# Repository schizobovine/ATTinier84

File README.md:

# ATTinier84
Smallish form factor ATTiny84 platform that doesn't bother with USB.

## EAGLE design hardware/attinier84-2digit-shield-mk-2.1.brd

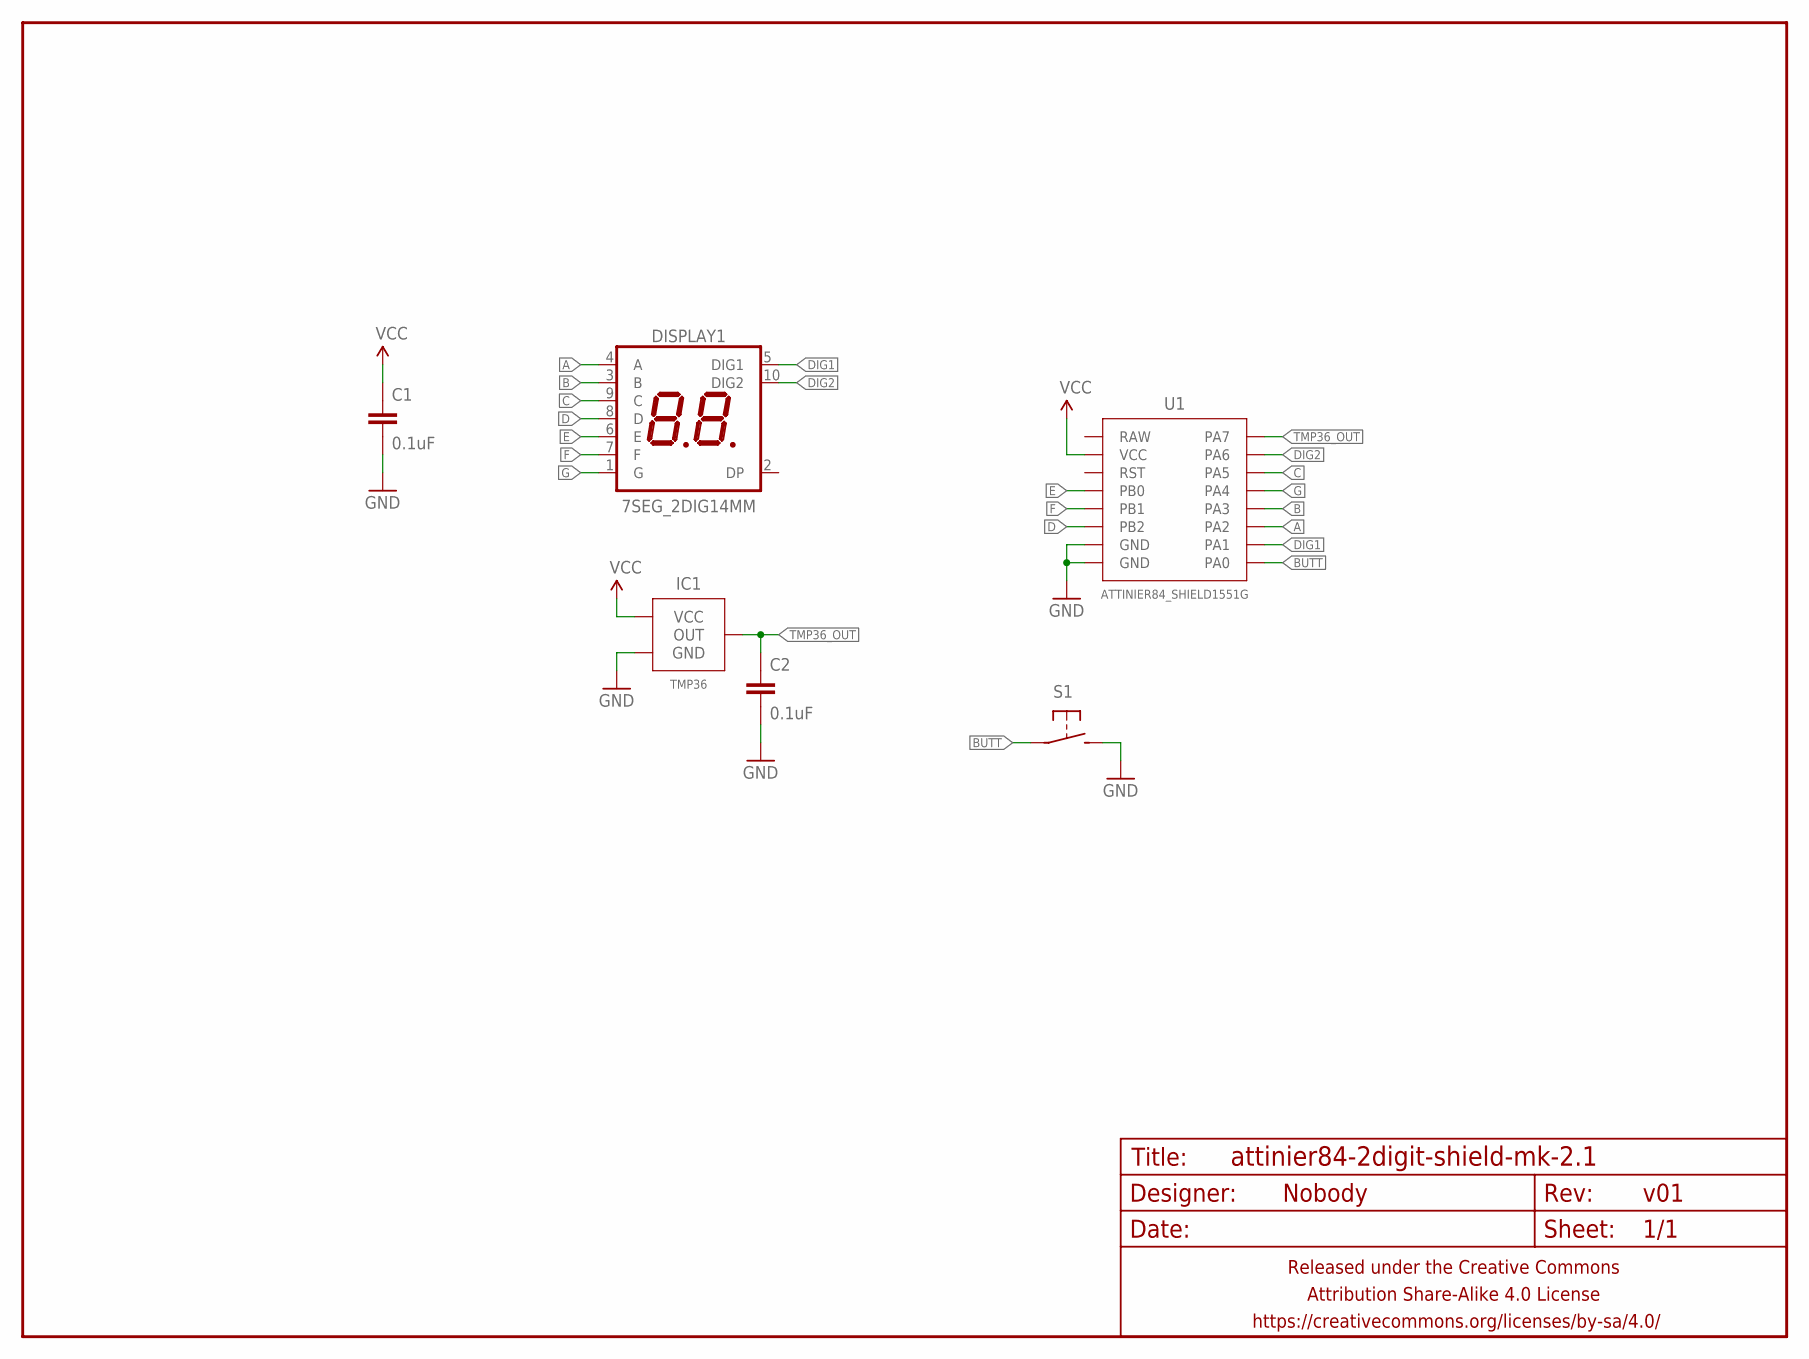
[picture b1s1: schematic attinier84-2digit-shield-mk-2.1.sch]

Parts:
C1, C2: 0.1uF; C025-024X044
DISPLAY1: 7SEG_2DIG14MM; 7SEG_2DIG_14MM
FRAME1: FRAME-LETTERNO_PACKAGE; DUMMY
IC1: TMP36; TO-92-AMMO
S1: SPST-NO-TACT3MM-PTH-SMALL-PADS; DTS-3-SMALL-PADS
U1: ATTINIER84_SHIELD1551G; ATTINIER84_SHIELD2

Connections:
A: DISPLAY1.4 (A), U1.PA2
B: DISPLAY1.3 (B), U1.PA3
BUTT: S1.1, U1.PA0
C: DISPLAY1.9 (C), U1.PA5
D: DISPLAY1.8 (D), U1.PB2
DIG1: DISPLAY1.5 (DIG1), U1.PA1
DIG2: DISPLAY1.10 (DIG2), U1.PA6
E: DISPLAY1.6 (E), U1.PB0
F: DISPLAY1.7 (F), U1.PB1
G: DISPLAY1.1 (G), U1.PA4
GND: C1.2, C2.2, IC1.3 (GND), S1.2, U1.GND@1 (GND), U1.GND@2 (GND)
TMP36_OUT: C2.1, IC1.2 (OUT), U1.PA7
VCC: C1.1, IC1.1 (VCC), U1.VCC

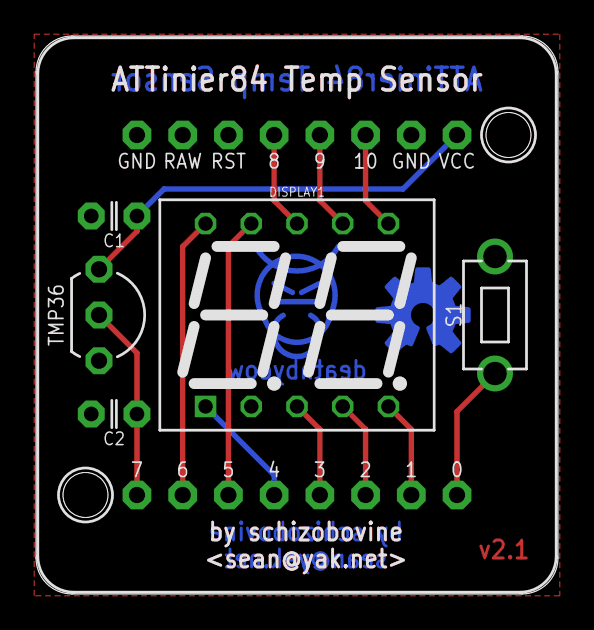
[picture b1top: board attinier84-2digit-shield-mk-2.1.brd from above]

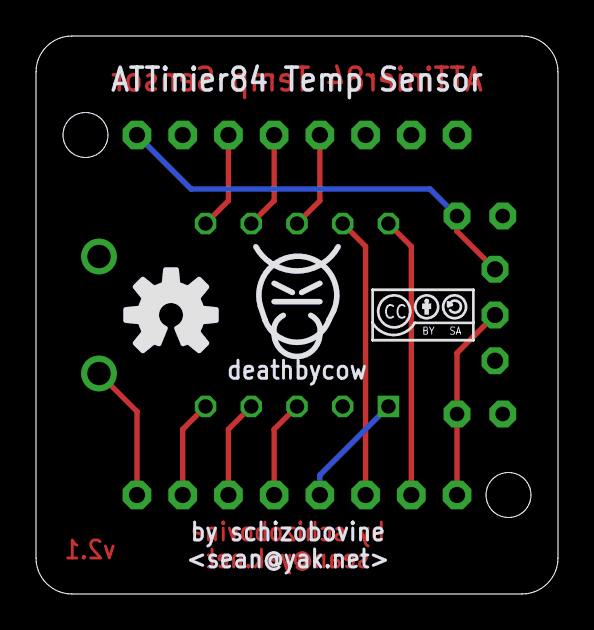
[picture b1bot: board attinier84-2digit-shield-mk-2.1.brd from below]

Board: 2 copper layers, 29.0 x 31.0 mm, 10 parts (2 on the bottom side), 13 nets.

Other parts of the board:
U$1: CC-BY-SA-4.0-NO-URL
U$2: COW_SMALL_METAL
U$3: OSHWLOGO_BOT_0.2_A

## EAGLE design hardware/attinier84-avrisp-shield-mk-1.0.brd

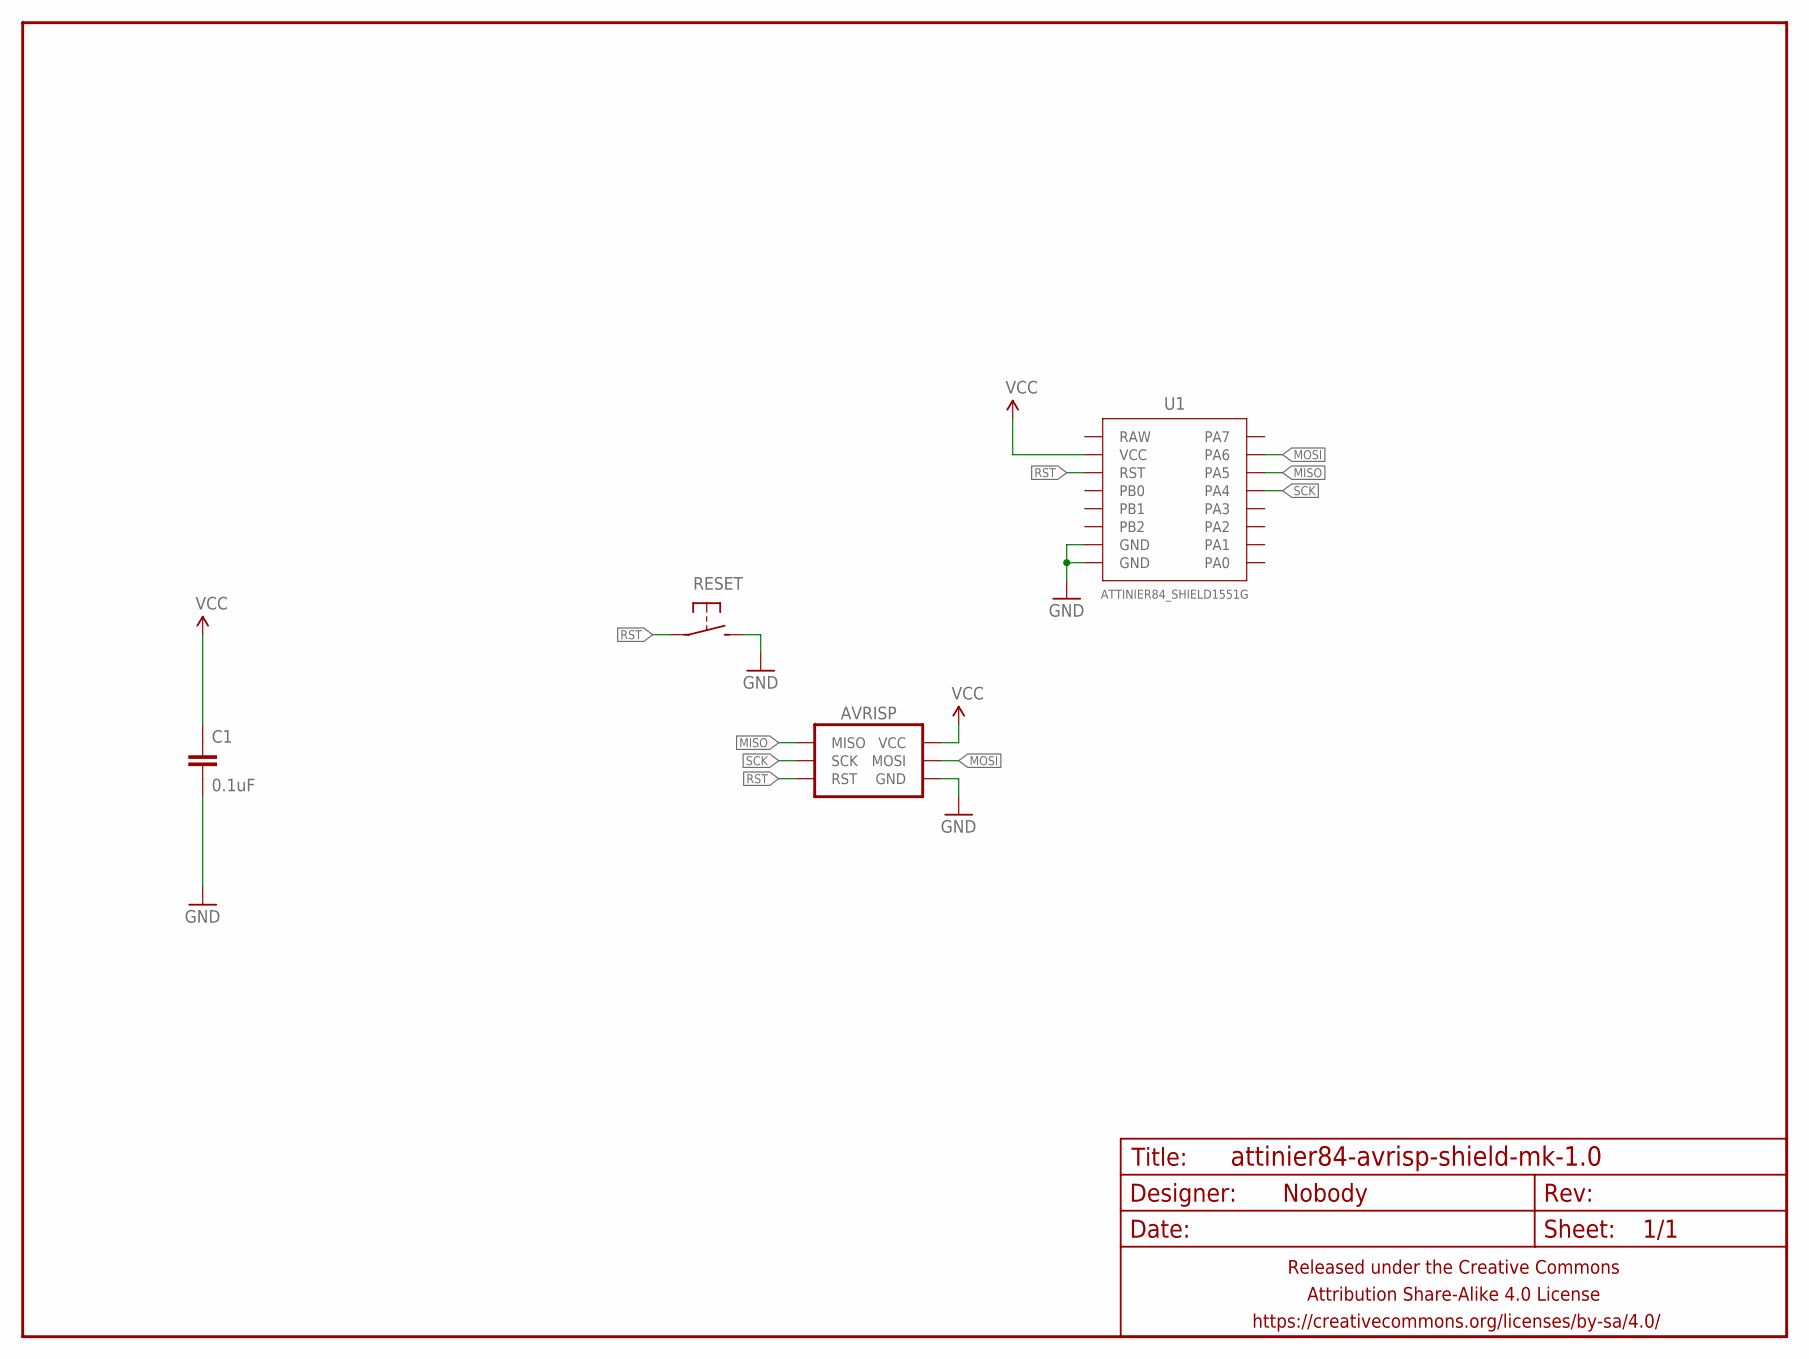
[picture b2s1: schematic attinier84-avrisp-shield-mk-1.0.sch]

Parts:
AVRISP: AVR_SPI_PRG_6PTH-SHROUD; 2X3-SHROUDED
C1: 0.1uF; C025-024X044
FRAME1: FRAME-LETTERNO_PACKAGE; DUMMY
RESET: SPST-NO-TACT6MM-PTH-SMALL-PADS; DTS-6-SMALL-PADS
U1: ATTINIER84_SHIELD1551G; ATTINIER84_SHIELD2

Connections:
GND: AVRISP.6 (GND), C1.2, RESET.3 (2), RESET.4 (2), U1.GND@1 (GND), U1.GND@2 (GND)
MISO: AVRISP.1 (MISO), U1.PA5
MOSI: AVRISP.4 (MOSI), U1.PA6
RST: AVRISP.5 (RST), RESET.1, RESET.2 (1), U1.RST
SCK: AVRISP.3 (SCK), U1.PA4
VCC: AVRISP.2 (VCC), C1.1, U1.VCC

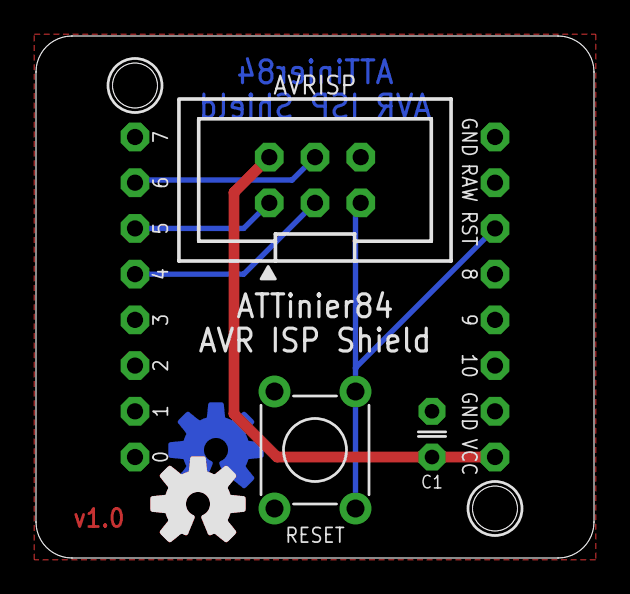
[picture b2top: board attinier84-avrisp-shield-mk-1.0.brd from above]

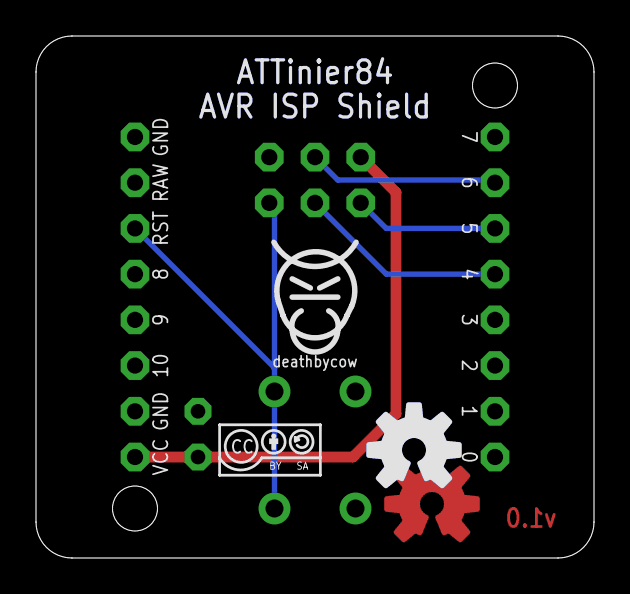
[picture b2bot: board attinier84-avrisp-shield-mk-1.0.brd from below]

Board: 2 copper layers, 31.0 x 29.0 mm, 9 parts (3 on the bottom side), 6 nets.

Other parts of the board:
U$1: CC-BY-SA-4.0-NO-URL
U$2: COW_SMALL
U$3, U$4: OSHWLOGO_BOT_0.2_A

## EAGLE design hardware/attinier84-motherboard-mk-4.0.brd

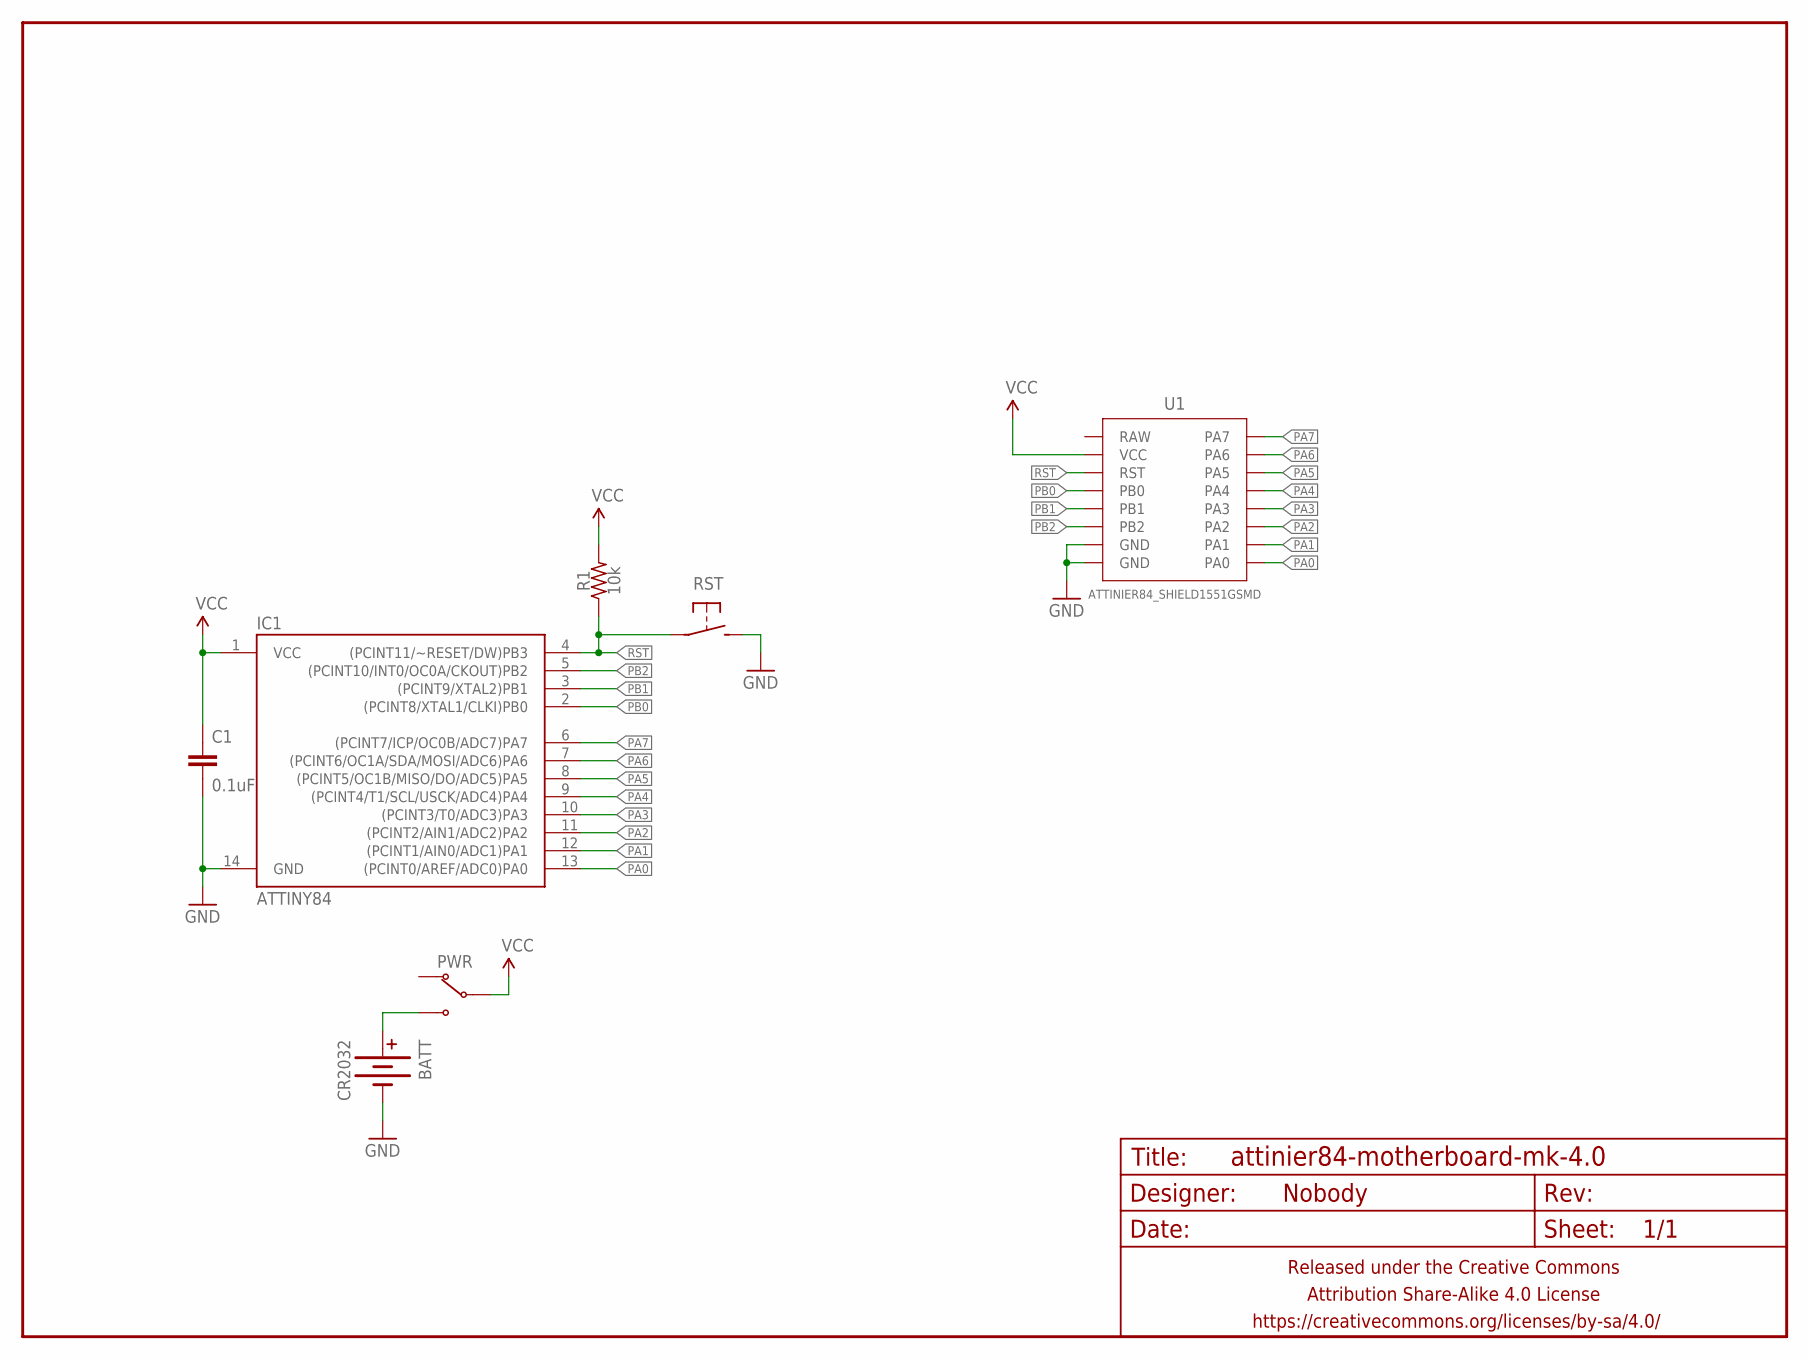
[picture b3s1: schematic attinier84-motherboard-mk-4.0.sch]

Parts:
BATT: CR2032; BATTCON_20MM_MINE_STAHPIT
C1: 0.1uF; C0805
FRAME1: FRAME-LETTERNO_PACKAGE; DUMMY
IC1: ATTINY84; SO14
PWR: SWITCH-SPDTPTH-RA-2.54MM; SPDT-RA-2.54MM
R1: 10k; R0805
RST: SPST-NO-TACTCK-PTS840-GK; TACTILE-SMD-CK-PTS840-GK
U1: ATTINIER84_SHIELD1551GSMD; ATTINIER84_SHIELD2_SMD

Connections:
GND: BATT.BOTTOM (-), C1.2, IC1.14 (GND), RST.3 (2), RST.4 (2), U1.GND@1 (GND), U1.GND@2 (GND)
unnamed: BATT.TOP@1 (+), BATT.TOP@2 (+), PWR.3 (NO)
PA0: IC1.13 ((PCINT0/AREF/ADC0)PA0), U1.PA0
PA1: IC1.12 ((PCINT1/AIN0/ADC1)PA1), U1.PA1
PA2: IC1.11 ((PCINT2/AIN1/ADC2)PA2), U1.PA2
PA3: IC1.10 ((PCINT3/T0/ADC3)PA3), U1.PA3
PA4: IC1.9 ((PCINT4/T1/SCL/USCK/ADC4)PA4), U1.PA4
PA5: IC1.8 ((PCINT5/OC1B/MISO/DO/ADC5)PA5), U1.PA5
PA6: IC1.7 ((PCINT6/OC1A/SDA/MOSI/ADC6)PA6), U1.PA6
PA7: IC1.6 ((PCINT7/ICP/OC0B/ADC7)PA7), U1.PA7
PB0: IC1.2 ((PCINT8/XTAL1/CLKI)PB0), U1.PB0
PB1: IC1.3 ((PCINT9/XTAL2)PB1), U1.PB1
PB2: IC1.5 ((PCINT10/INT0/OC0A/CKOUT)PB2), U1.PB2
RST: IC1.4 ((PCINT11/~RESET/DW)PB3), R1.1, RST.1, RST.2 (1), U1.RST
VCC: C1.1, IC1.1 (VCC), PWR.2 (COM), R1.2, U1.VCC

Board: 2 copper layers, 11 parts (3 on the bottom side), 15 nets, no tracks yet.

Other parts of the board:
U$1: CC-BY-SA-4.0-NO-URL
U$2: COW_SMALL
U$4: OSHWLOGO_BOT_0.2_A

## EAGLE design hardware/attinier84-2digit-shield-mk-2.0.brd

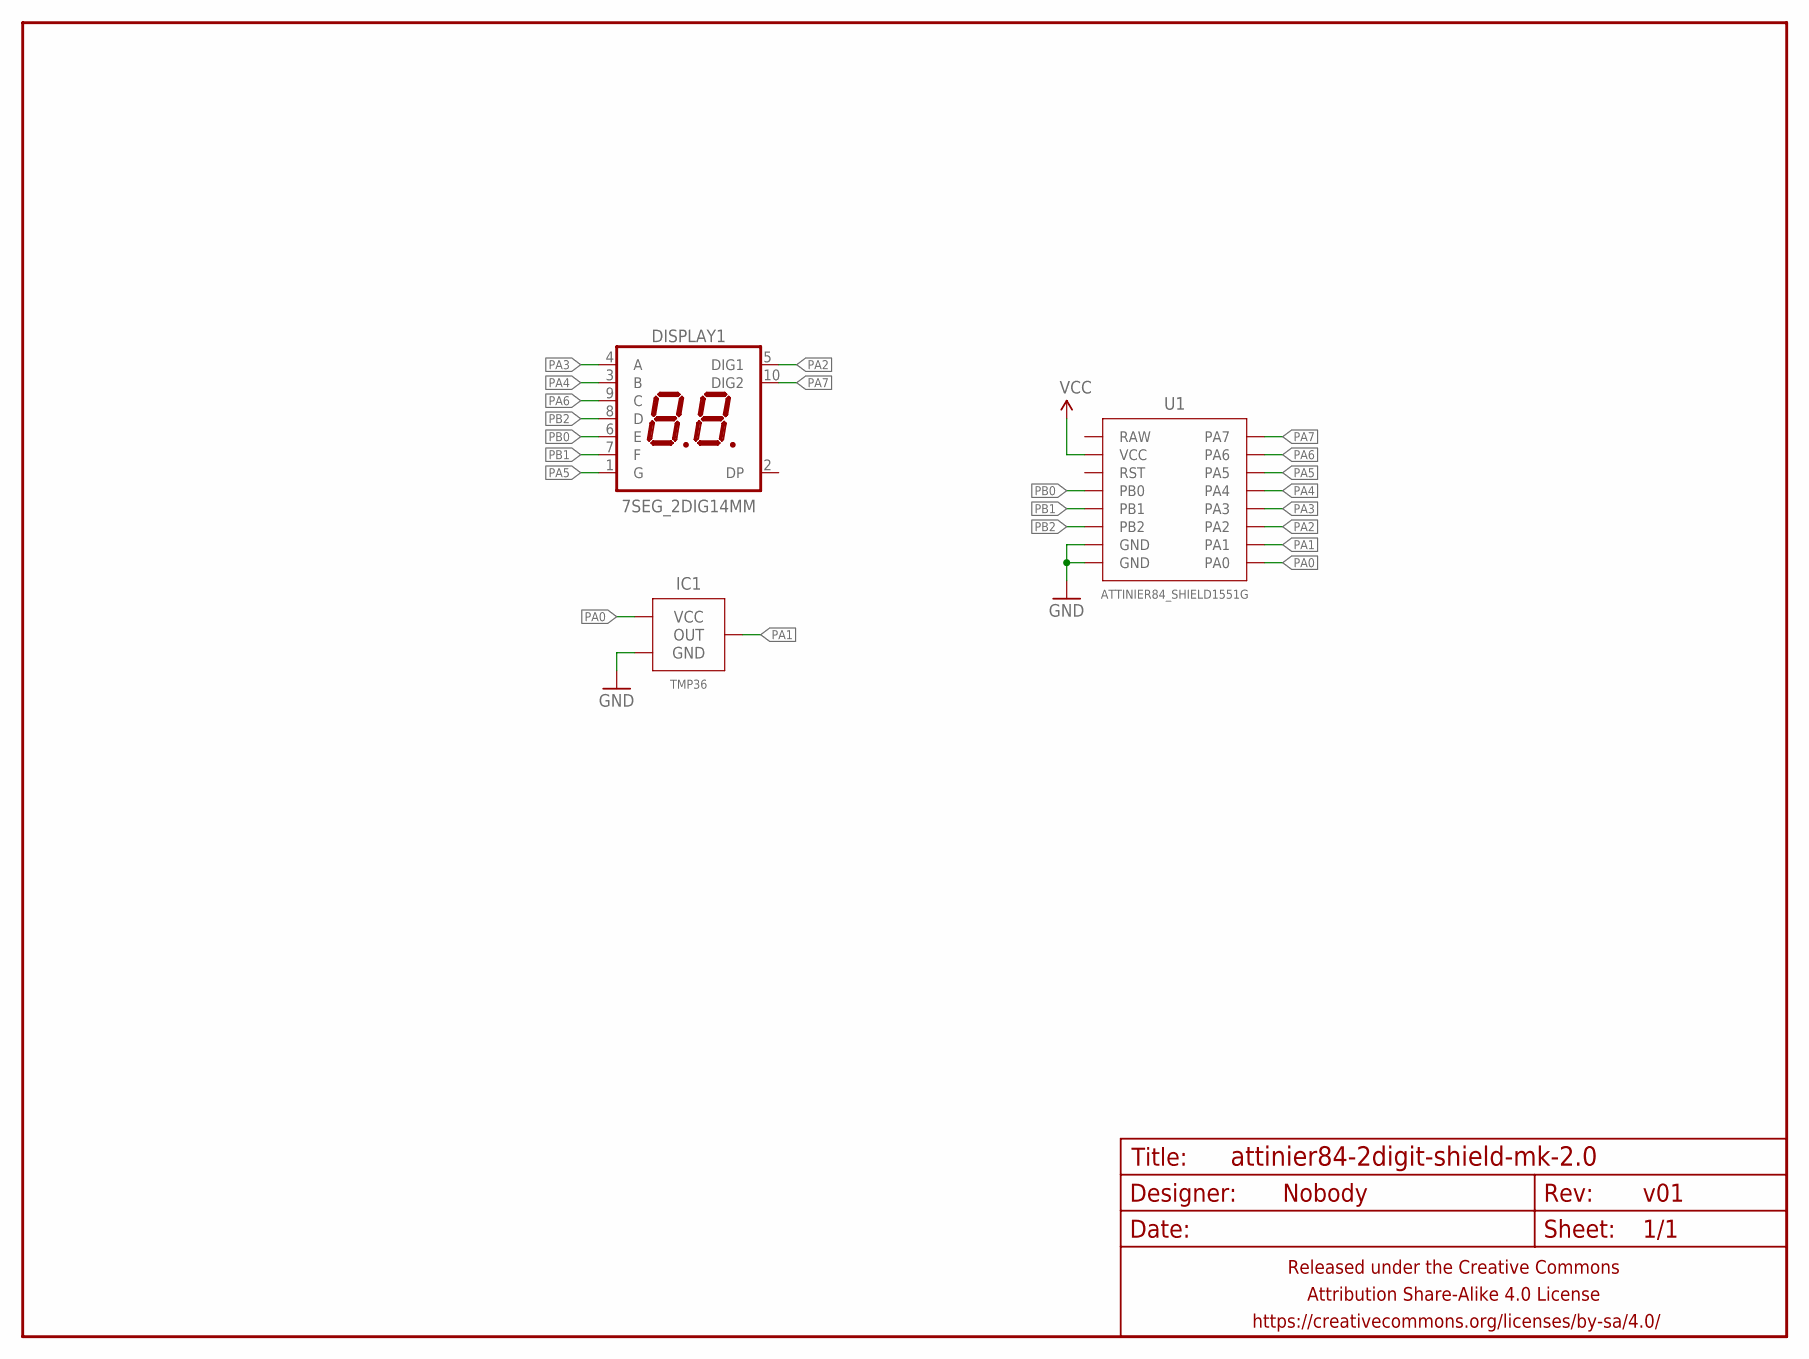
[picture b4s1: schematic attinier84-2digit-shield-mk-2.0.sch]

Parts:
DISPLAY1: 7SEG_2DIG14MM; 7SEG_2DIG_14MM
FRAME1: FRAME-LETTERNO_PACKAGE; DUMMY
IC1: TMP36; TO-92-AMMO
U1: ATTINIER84_SHIELD1551G; ATTINIER84_SHIELD2

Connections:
GND: IC1.3 (GND), U1.GND@1 (GND), U1.GND@2 (GND)
PA0: IC1.1 (VCC), U1.PA0
PA1: IC1.2 (OUT), U1.PA1
PA2: DISPLAY1.5 (DIG1), U1.PA2
PA3: DISPLAY1.4 (A), U1.PA3
PA4: DISPLAY1.3 (B), U1.PA4
PA5: DISPLAY1.1 (G), U1.PA5
PA6: DISPLAY1.9 (C), U1.PA6
PA7: DISPLAY1.10 (DIG2), U1.PA7
PB0: DISPLAY1.6 (E), U1.PB0
PB1: DISPLAY1.7 (F), U1.PB1
PB2: DISPLAY1.8 (D), U1.PB2
VCC: U1.VCC

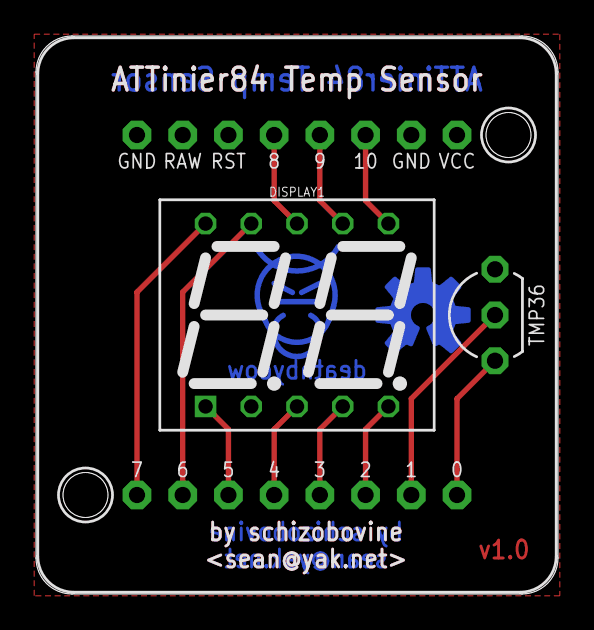
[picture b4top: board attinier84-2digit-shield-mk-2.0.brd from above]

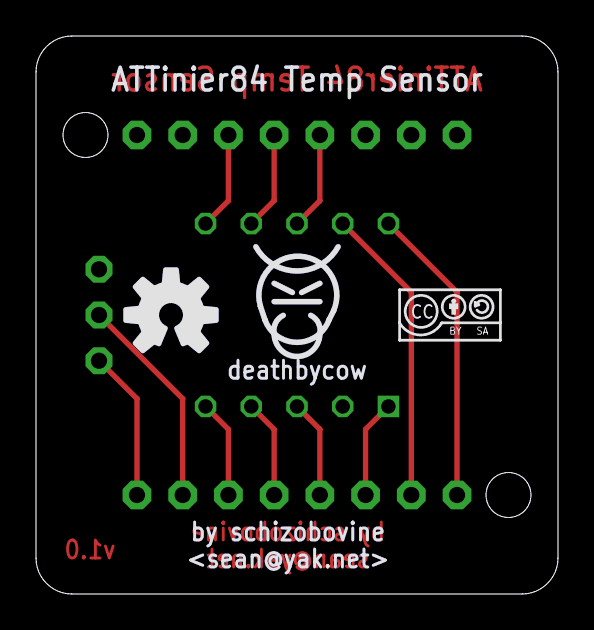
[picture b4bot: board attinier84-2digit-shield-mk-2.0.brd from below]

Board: 2 copper layers, 29.0 x 31.0 mm, 7 parts (2 on the bottom side), 12 nets.

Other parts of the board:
U$1: CC-BY-SA-4.0-NO-URL
U$2: COW_SMALL_METAL
U$3: OSHWLOGO_BOT_0.2_A

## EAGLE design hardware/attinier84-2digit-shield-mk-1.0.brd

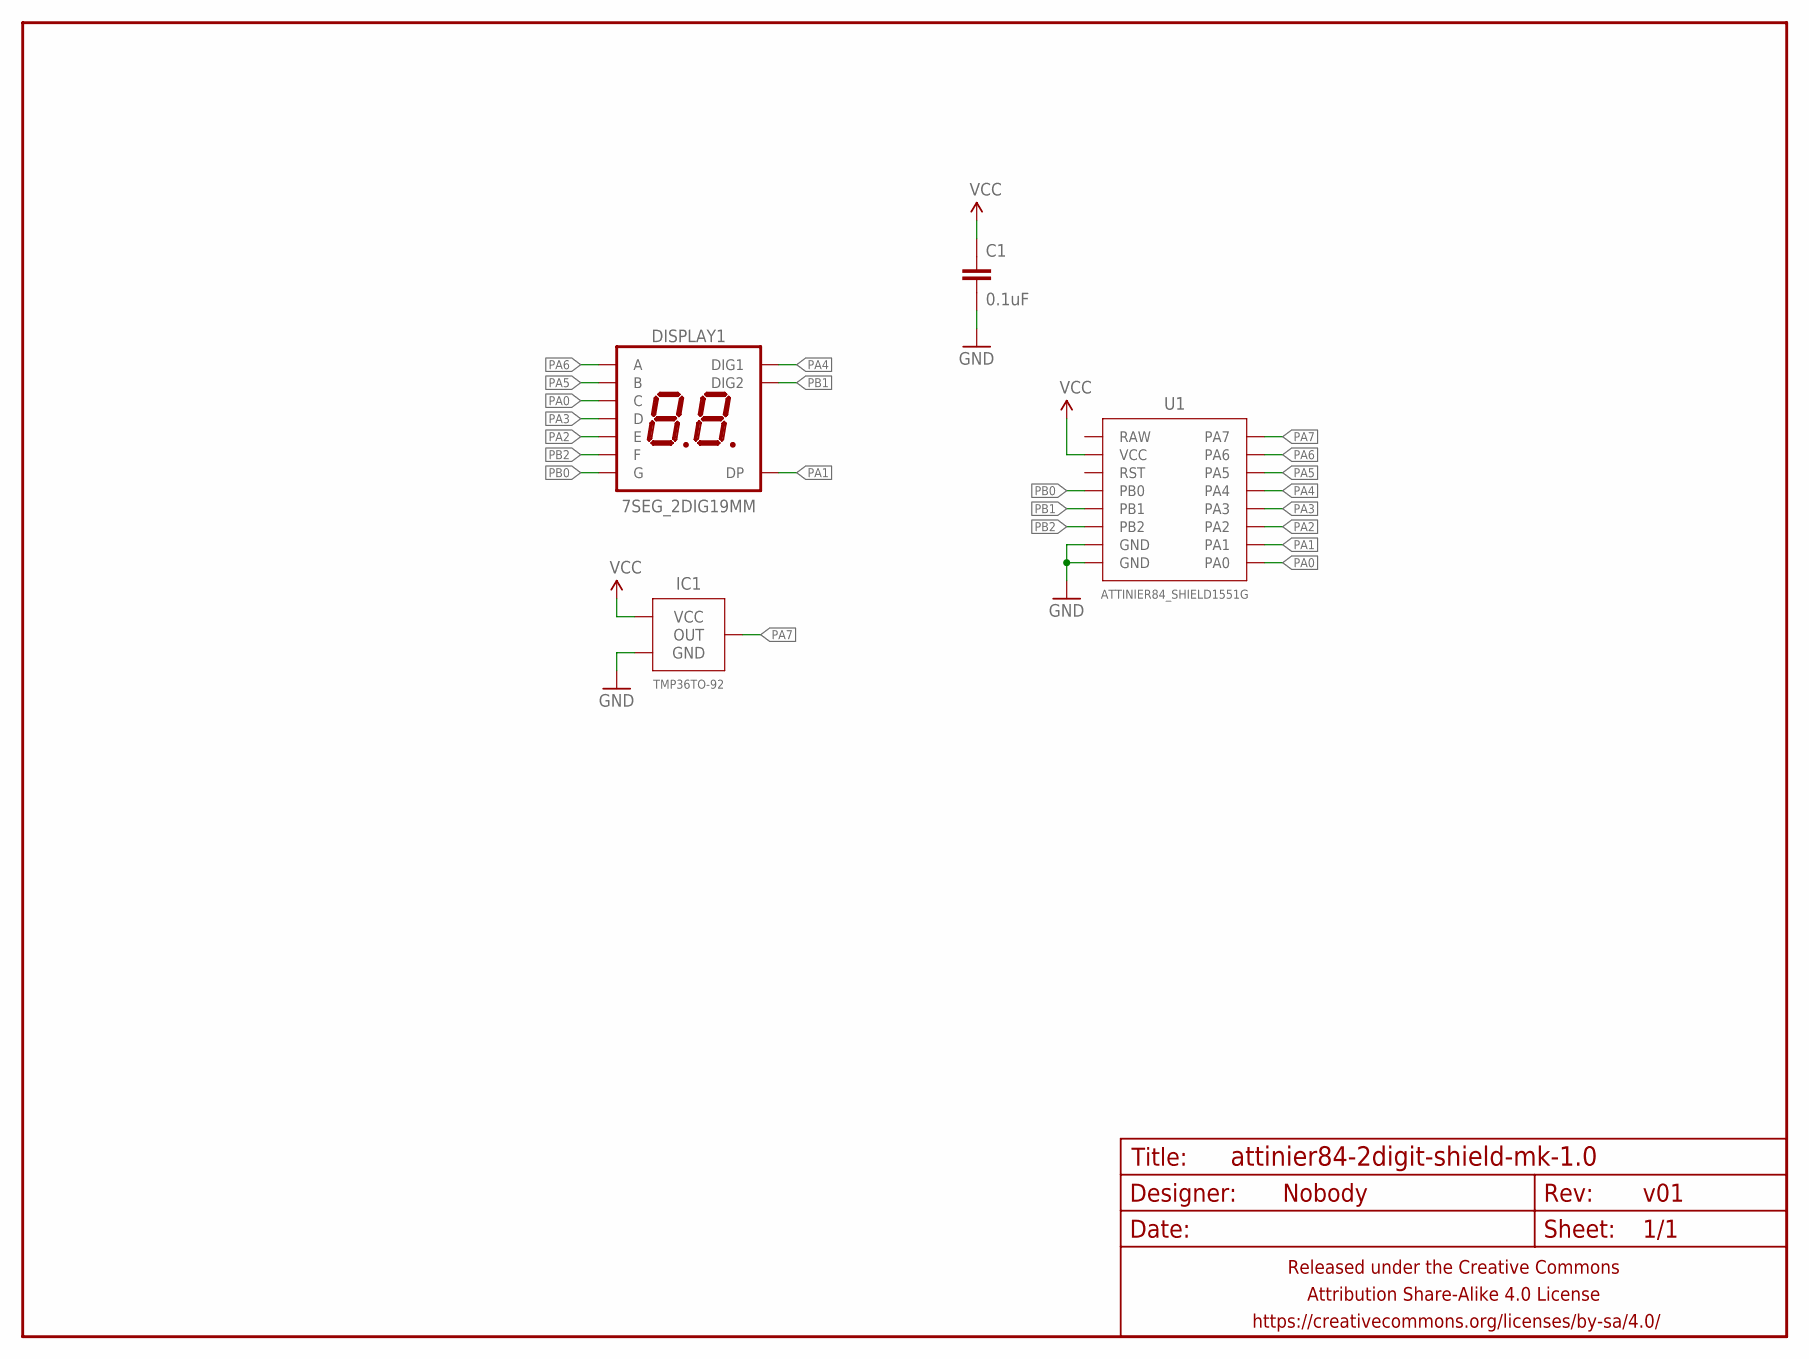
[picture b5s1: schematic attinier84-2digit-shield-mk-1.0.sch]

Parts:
C1: 0.1uF; C025-024X044
DISPLAY1: 7SEG_2DIG19MM; 7SEG_2DIG_19MM
FRAME1: FRAME-LETTERNO_PACKAGE; DUMMY
IC1: TMP36TO-92; TO-92-AMMO
U1: ATTINIER84_SHIELD1551G; ATTINIER84_SHIELD2

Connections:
GND: C1.2, IC1.3 (GND), U1.GND@1 (GND), U1.GND@2 (GND)
PA0: DISPLAY1.1 (C), U1.PA0
PA1: DISPLAY1.2 (DP), U1.PA1
PA2: DISPLAY1.3 (E), U1.PA2
PA3: DISPLAY1.4 (D), U1.PA3
PA4: DISPLAY1.8 (DIG1), U1.PA4
PA5: DISPLAY1.9 (B), U1.PA5
PA6: DISPLAY1.10 (A), U1.PA6
PA7: IC1.2 (OUT), U1.PA7
PB0: DISPLAY1.5 (G), U1.PB0
PB1: DISPLAY1.7 (DIG2), U1.PB1
PB2: DISPLAY1.6 (F), U1.PB2
VCC: C1.1, IC1.1 (VCC), U1.VCC

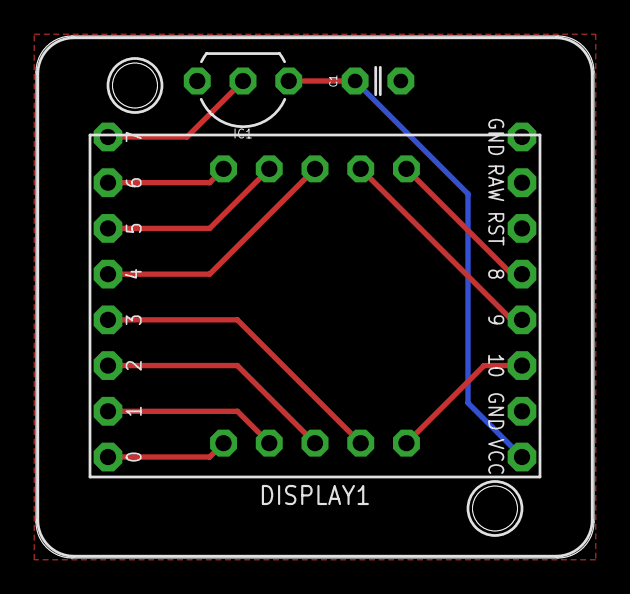
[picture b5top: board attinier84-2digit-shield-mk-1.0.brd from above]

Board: 2 copper layers, 31.0 x 29.0 mm, 5 parts (0 on the bottom side), 13 nets.

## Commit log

2015-05-08 whole bunch o crap
2015-05-08 finished up motherboard, initial shield dicking
2015-05-08 temp shield with display done
2015-05-11 PTH version
2015-05-11 adding ISP header
2015-05-25 initial commit of some stupid simple 7 seg code
2015-05-26 alkfjdlasfkj
2015-05-28 initial firmware plus firmware to determine bandgap value (need to figure out how to merge & automate that)
2015-05-28 rejigger pinout, general purpose button, swap positions with temp sensor and button, hook temp sensor directly to vcc
2015-06-27 SMT ALL THE THINGS
2015-06-29 small tweak to capacitor layout
2015-08-10 HOW I MAKEFILE

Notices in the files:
parts and their libraries:
A_butts: Released under the Creative Commons Attribution Share-Alike 4.0 License
A_butts: https://creativecommons.org/licenses/by-sa/4.0
A_butts: Released under the Creative Commons
